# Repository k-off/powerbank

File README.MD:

# PowerBank

Minimal DIY power bank with USB-C and fast charging.

## Overview

This minimal DIY power bank features a custom-designed case created in Fusion 360 to securely hold four 18650 lithium-ion cells, providing a robust and compact power source. The enclosure is tailored to fit the battery pack and the custom PCB, ensuring a neat and durable assembly. The PCB, designed in KiCad, incorporates the IP2312 charging IC for safe and efficient battery charging and the Texas Instruments TPS61022 boost converter to step up the battery voltage to a stable 5 V output. Both the USB-C input and output ports support up to 3A current, enabling fast charging and discharging capabilities suitable for modern devices.

The TPS61022 boost converter is a high-efficiency synchronous step-up converter capable of delivering 5 V at 3 A with an input voltage range from 0.5 V to 5.5 V, making it ideal for single-cell lithium-ion battery applications. It operates at a high switching frequency (up to 1 MHz) for low ripple and efficient power conversion, and includes protections such as overvoltage, thermal shutdown, and short-circuit protection.

The IP2312 charging IC manages the charging process of the 18650 cells, ensuring battery safety and longevity.

The power bank includes simple charge indicators showing charging in process and completion, though it currently lacks device charging or battery state indicators, maintaining a minimalist design focused on core functionality. This DIY power bank is ideal for enthusiasts seeking a custom, efficient, and compact portable power solution.

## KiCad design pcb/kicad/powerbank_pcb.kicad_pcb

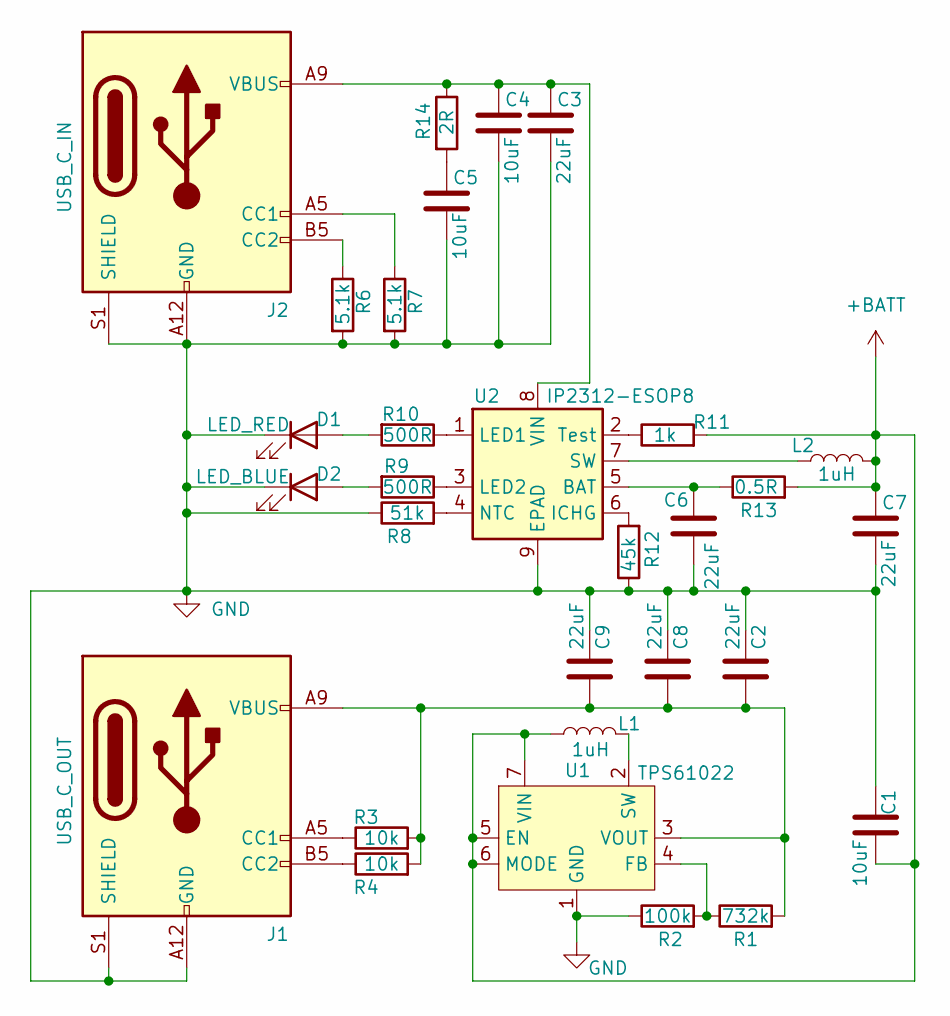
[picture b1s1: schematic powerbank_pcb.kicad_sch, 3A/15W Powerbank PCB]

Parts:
C1, C4, C5: 10uF; C_0805_2012Metric_Pad1.18x1.45mm_HandSolder
C2: 22uF
C3, C6, C7, C8, C9: 22uF; C_0805_2012Metric_Pad1.18x1.45mm_HandSolder
D1: LED_RED; LED_0805_2012Metric_Pad1.15x1.40mm_HandSolder
D2: LED_BLUE; LED_0805_2012Metric_Pad1.15x1.40mm_HandSolder
J1: USB_C_OUT; USB_C_Receptacle_GCT_USB4125-xx-x_6P_TopMnt_Horizontal
J2: USB_C_IN; USB_C_Receptacle_GCT_USB4125-xx-x_6P_TopMnt_Horizontal
L1, L2: 1uH; L_Coilcraft_XxL4030
R1: 732k; R_0805_2012Metric_Pad1.20x1.40mm_HandSolder
R2: 100k; R_0805_2012Metric_Pad1.20x1.40mm_HandSolder
R3, R4: 10k; R_0805_2012Metric_Pad1.20x1.40mm_HandSolder
R6, R7: 5.1k; R_0805_2012Metric_Pad1.20x1.40mm_HandSolder
R8: 51k; R_0805_2012Metric_Pad1.20x1.40mm_HandSolder
R9, R10: 500R; R_0805_2012Metric_Pad1.20x1.40mm_HandSolder
R11: 1k; R_0805_2012Metric_Pad1.20x1.40mm_HandSolder
R12: 45k; R_0805_2012Metric_Pad1.20x1.40mm_HandSolder
R13: 0.5R; R_0805_2012Metric_Pad1.20x1.40mm_HandSolder
R14: 2R; R_0805_2012Metric_Pad1.20x1.40mm_HandSolder
U1: TPS61022; Texas_RWU0007A_VQFN-7_2x2mm_P0.5mm
U2: IP2312-ESOP8; SOIC-8-1EP_3.9x4.9mm_P1.27mm_EP2.41x3.3mm_ThermalVias

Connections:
+BATT: C1.1, C7.1, L1.1, L2.2, R11.2, R13.2, U1.5 (EN), U1.6 (MODE), U1.7 (VIN)
GND: C1.2, C2.1, C3.2, C4.2, C5.2, C6.2, C7.2, C8.1, C9.1, D1.1 (K), D2.1 (K), J1.A12 (GND), J1.B12 (GND), J1.S1 (SHIELD), J2.A12 (GND), J2.B12 (GND), J2.S1 (SHIELD), R2.1, R6.2, R7.2, R8.1, R12.1, U1.1 (GND), U2.9 (EPAD)
unnamed: C5.1, R14.2
unnamed: D1.2 (A), R10.2
unnamed: D2.2 (A), R9.2
unnamed: J1.A5 (CC1), R3.1
unnamed: J1.B5 (CC2), R4.1
unnamed: J2.A5 (CC1), R7.1
unnamed: J2.B5 (CC2), R6.1
unnamed: R1.1, R2.2, U1.4 (FB)
unnamed: L1.2, U1.2 (SW)
unnamed: C2.2, C8.2, C9.2, J1.A9 (VBUS), J1.B9 (VBUS), R1.2, R3.2, R4.2, U1.3 (VOUT)
unnamed: C6.1, R13.1, U2.5 (BAT)
unnamed: R12.2, U2.6 (ICHG)
unnamed: R10.1, U2.1 (LED1)
unnamed: R9.1, U2.3 (LED2)
unnamed: R8.2, U2.4 (NTC)
unnamed: L2.1, U2.7 (SW)
unnamed: R11.1, U2.2 (Test)
unnamed: C3.1, C4.1, J2.A9 (VBUS), J2.B9 (VBUS), R14.1, U2.8 (VIN)

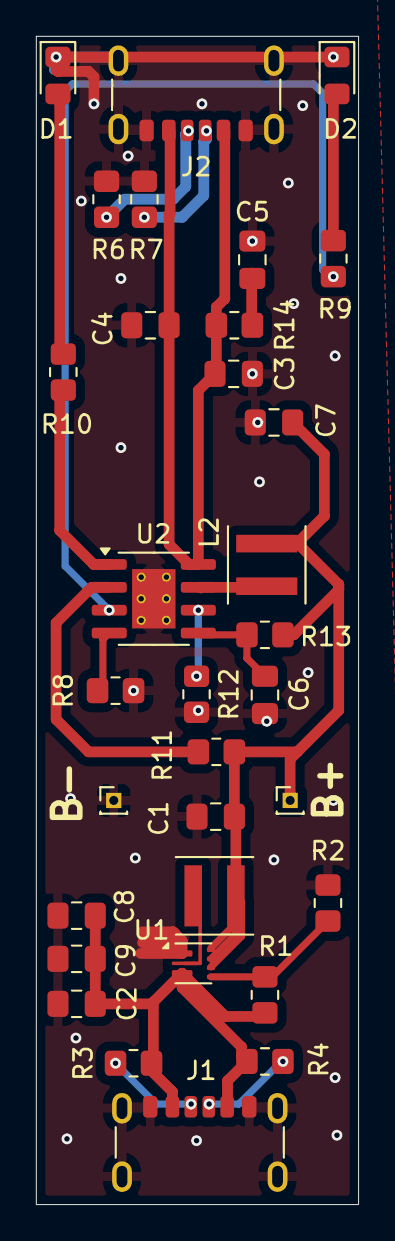
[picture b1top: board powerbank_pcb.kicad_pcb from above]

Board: 2 copper layers, 17.9 x 64.9 mm, 30 parts (0 on the bottom side), 20 nets.

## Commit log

2025-06-14 v0.0.1a
2025-06-14 add readme
